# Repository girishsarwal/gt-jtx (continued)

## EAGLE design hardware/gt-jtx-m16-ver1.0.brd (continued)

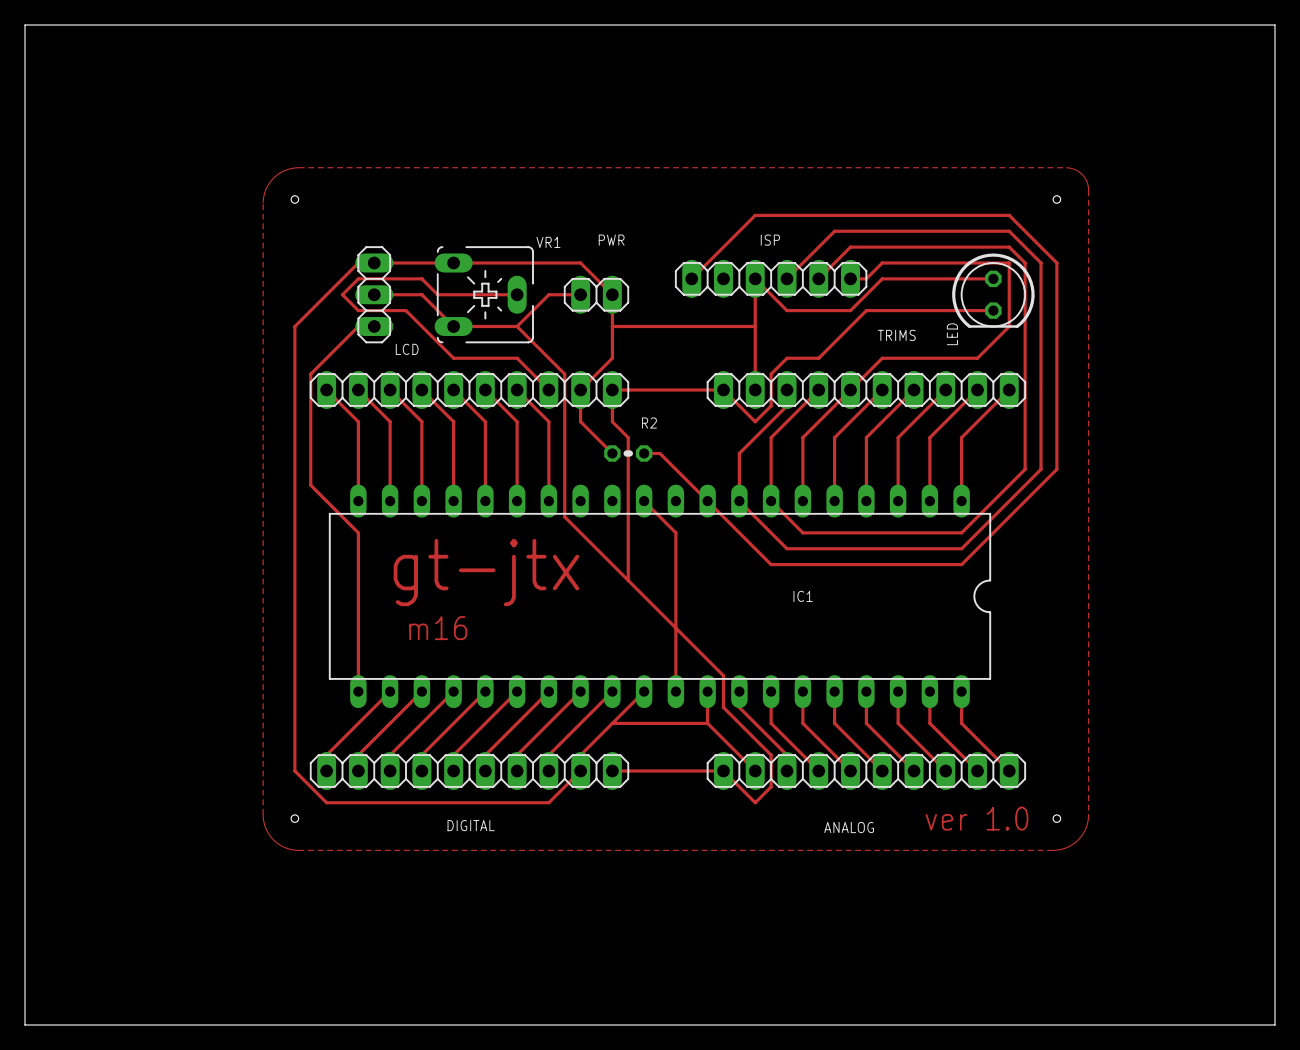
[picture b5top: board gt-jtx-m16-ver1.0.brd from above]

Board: 2 copper layers, 100.0 x 80.0 mm, 11 parts (0 on the bottom side), 36 nets.

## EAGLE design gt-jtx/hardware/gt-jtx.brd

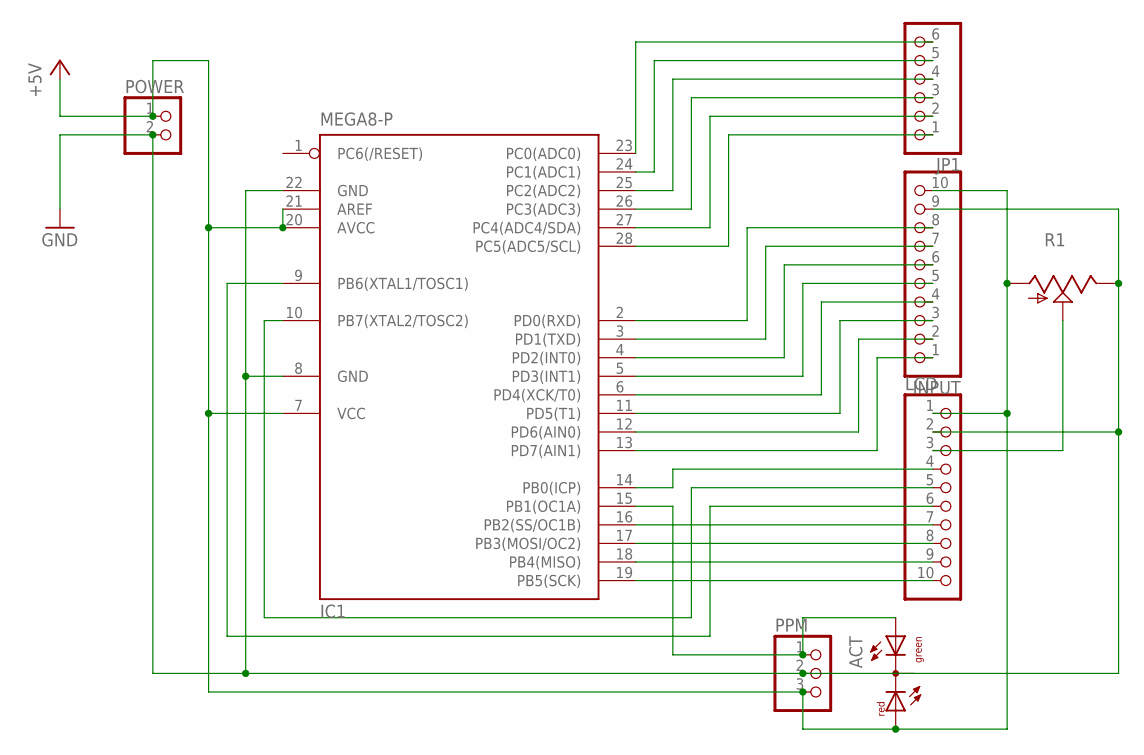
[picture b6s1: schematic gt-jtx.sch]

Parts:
ACT: DUOLED-RG-C; DUOLED-C-5MM
IC1: MEGA8-P; DIL28-3
INPUT: PINHD-1X10; 1X10
JP1: PINHD-1X6; 1X06
LCD: PINHD-1X10; 1X10
POWER: PINHD-1X2; 1X02
PPM: PINHD-1X3; 1X03
R1: TRIM_US-CA6V; CA6V

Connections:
+5V: ACT.AR, IC1.7 (VCC), IC1.20 (AVCC), IC1.21 (AREF), INPUT.10, LCD.1, POWER.1, PPM.3, R1.A; also elsewhere on the board
GND: ACT.C, IC1.8 (GND), IC1.22 (GND), INPUT.9, LCD.2, POWER.2, PPM.2, R1.E
unnamed: IC1.23 (PC0(ADC0)), JP1.6
unnamed: IC1.24 (PC1(ADC1)), JP1.5
unnamed: IC1.25 (PC2(ADC2)), JP1.4
unnamed: IC1.26 (PC3(ADC3)), JP1.3
unnamed: IC1.14 (PB0(ICP)), LCD.4
unnamed: IC1.10 (PB7(XTAL2/TOSC2)), LCD.5
unnamed: IC1.9 (PB6(XTAL1/TOSC1)), LCD.6
unnamed: IC1.2 (PD0(RXD)), INPUT.8
unnamed: LCD.3, R1.S
unnamed: IC1.27 (PC4(ADC4/SDA)), JP1.2
unnamed: IC1.28 (PC5(ADC5/SCL)), JP1.1
unnamed: IC1.19 (PB5(SCK)), LCD.10
unnamed: IC1.18 (PB4(MISO)), LCD.9
unnamed: IC1.17 (PB3(MOSI/OC2)), LCD.8
unnamed: IC1.16 (PB2(SS/OC1B)), LCD.7
unnamed: ACT.AX (AG), IC1.15 (PB1(OC1A)), PPM.1
unnamed: IC1.3 (PD1(TXD)), INPUT.7
unnamed: IC1.4 (PD2(INT0)), INPUT.6
unnamed: IC1.5 (PD3(INT1)), INPUT.5
unnamed: IC1.6 (PD4(XCK/T0)), INPUT.4
unnamed: IC1.11 (PD5(T1)), INPUT.3
unnamed: IC1.13 (PD7(AIN1)), INPUT.1
unnamed: IC1.12 (PD6(AIN0)), INPUT.2
unnamed 26: IC1.1 (PC6(/RESET)); also elsewhere on the board

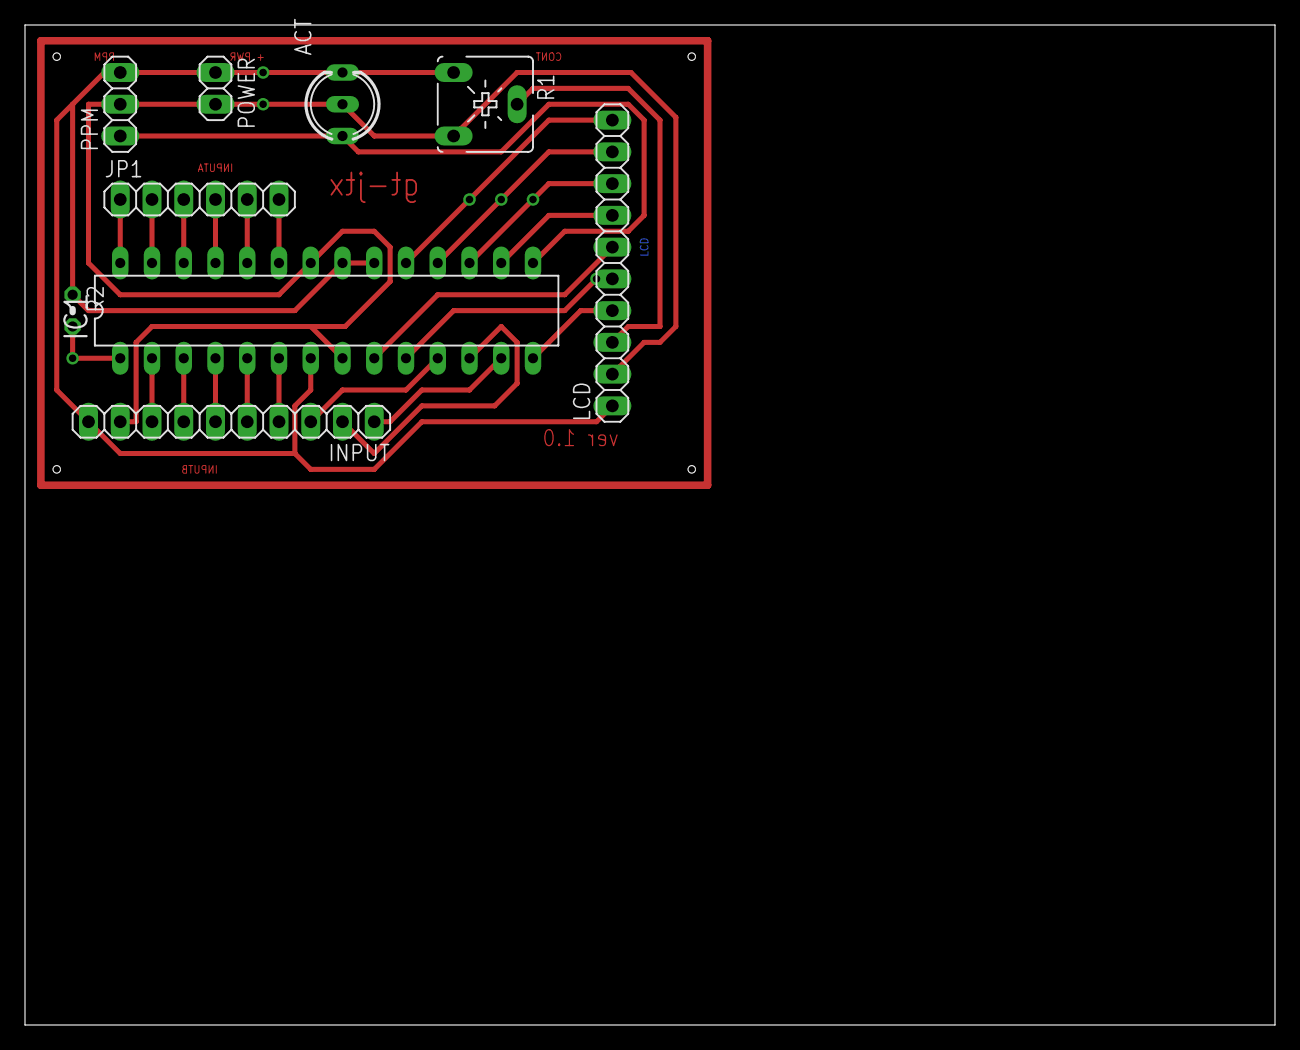
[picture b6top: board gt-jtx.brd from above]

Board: 2 copper layers, 100.0 x 80.0 mm, 9 parts (0 on the bottom side), 26 nets.

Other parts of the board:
R2: 0204V

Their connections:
+5V: R2.1; also elsewhere on the board
unnamed 26: R2.2; also elsewhere on the board

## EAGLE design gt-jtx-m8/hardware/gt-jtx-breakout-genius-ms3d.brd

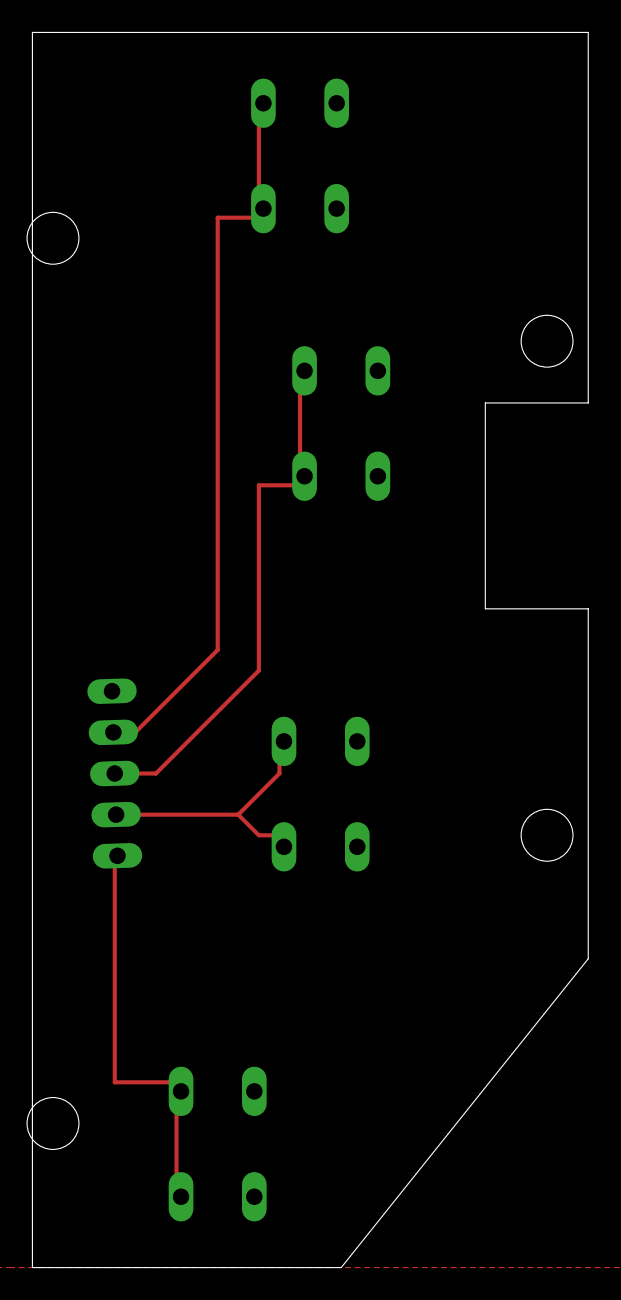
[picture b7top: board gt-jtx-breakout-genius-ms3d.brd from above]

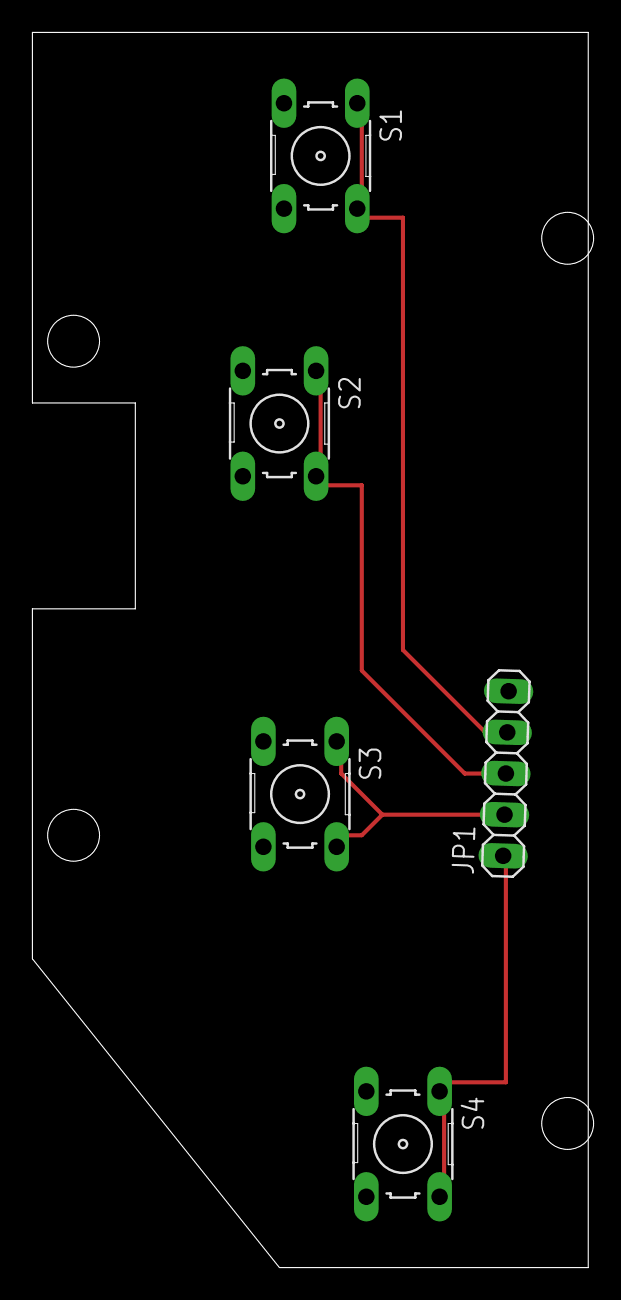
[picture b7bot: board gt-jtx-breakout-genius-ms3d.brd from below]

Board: 2 copper layers, 34.3 x 76.2 mm, 5 parts (5 on the bottom side), 5 nets.

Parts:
JP1: 1X05
S1, S2, S3, S4: B3F-10XX

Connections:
GND: JP1.5, S1.3, S1.4, S2.3, S2.4, S3.3, S3.4, S4.3, S4.4
unnamed: JP1.2, S3.1, S3.2
unnamed: JP1.1, S4.1, S4.2
unnamed: JP1.4, S1.1, S1.2
unnamed: JP1.3, S2.1, S2.2

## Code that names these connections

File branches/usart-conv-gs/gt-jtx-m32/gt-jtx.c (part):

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#define MAGIC_NUMBER 0xA0


#define INP1		0    //Mapped to PA7
#define INP2		1    //Mapped to PA6
#define INP3		2    //Mapped to PA5
#define INP4		3    //Mapped to PA4
#define INP5 		4    //Mapped to PA3
#define INP6		5    //Mapped to PA2
#define INP7		6    //Mapped to PA1
#define INP8		7    //Mapped to PA0

#define MAX_ANALOG_INPUTS 8

#define INP9		8     //Mapped to PD6
#define INP10		9     //Mapped to PD3
#define INP11		10    //Mapped to PD2
#define INP12		11    //Mapped to PB4
#define INP13		12    //Mapped to PB3
#define INP14		13    //Mapped to PB2
#define INP15		14    //Mapped to PB1
#define INP16		15     //Mapped to PB0

#define MAX_DIGITAL_INPUTS 8

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	/** setup the SPI Slave **/
	/** Port B has the MISO/MOSI pins. Setup MOSI as input **/
	transaction.state = WAIT_OPCODE;
	DDRB = (1<<PB6);	/**Setup MISO as output */
	SPCR = (1<<SPE) | (1<<SPIE) | (1<<SPR0) | (1<<SPR1)| (1<<CPOL);	/** enable SPI **/
	SPDR = 0xFF;
	sei();
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	DDR_ANALOG = 0x00;						
	PORT_ANALOG = 0x00;				/**Deactivate any pull ups **/
											/**
											 ** PC0 = AIL Input
											 ** PC1 = ELE Input
											 ** PC2 = THR Input
											 ** PC3 = RUD Input
											 ** PC4 = CH5 Input
											 ** PC5 - CH6 Input
											 ** PC6 - CH7 Input
											 ** PC7 - Ch8 Input
											**/
 	
 	/** Trim switches **/
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
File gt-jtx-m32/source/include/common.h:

/*
 * common.h
 *
 *  Created on: 22-May-2018
 *      Author: Girish Sarwal
 *      Email:  g.sarwal@gmail.com
 *      	 , 	girish.sarwal@gluedtomatoes.com
 */

#ifndef _COMMON_H_
#define _COMMON_H_

#ifndef F_CPU
#define F_CPU 1000000UL
#endif

#define BAUDRATE 19200	/** USART Baudrate **/
#define UBRRVAL ((F_CPU/(BAUDRATE*16UL))-1)

#define DEBUG

#include <avr/io.h>
#include <util/delay.h>
#include <avr/eeprom.h>
#include <avr/interrupt.h>
#include <math.h>

/** Analog inputs are 0-7 on Port A**/
#define PORT_ANALOG	PORTA
#define DDR_ANALOG	DDRA
#define PIN_ANALOG	PINA

#define AI0		0    //Mapped to PA0
#define AI1		1    //Mapped to PA1
#define AI2		2    //Mapped to PA2
#define AI3		3    //Mapped to PA3
#define AI4 	4    //Mapped to PA4
#define AI5		5    //Mapped to PA5
#define AI6		6    //Mapped to PA6
#define AI7		7    //Mapped to PA7


#define NUM_ANALOG_INPUTS 8

#define PORT_DIGITAL	PORTB
#define DDR_DIGITAL		DDRB
#define PIN_DIGITAL		PINB

/** Digital inputs are 0-7 on Port B **/
#define DI0		0    //Mapped to PB0
#define DI1		1    //Mapped to PB1
#define DI2		2    //Mapped to PB2
#define DI3		3    //Mapped to PB3
#define DI4 	4    //Mapped to PB4
#define DI5		5    //Mapped to PB5
#define DI6		6    //Mapped to PB6
#define DI7		7    //Mapped to PB7

#define NUM_DIGITAL_INPUTS 8

#define NUM_PHYSICAL_INPUTS (NUM_ANALOG_INPUTS + NUM_DIGITAL_INPUTS)

#define	INP0 	AI0
#define INP1	AI1
#define INP2	AI2
#define INP3	AI3
#define INP4	AI4
#define INP5	AI5
#define INP6	AI6
#define INP7	AI7

#define INP8	NUM_ANALOG_INPUTS + DI0
#define INP9	NUM_ANALOG_INPUTS + DI1
#define INP10	NUM_ANALOG_INPUTS + DI2
#define INP11	NUM_ANALOG_INPUTS + DI3
#define INP12	NUM_ANALOG_INPUTS + DI4
#define INP13	NUM_ANALOG_INPUTS + DI5
#define INP14	NUM_ANALOG_INPUTS + DI6
#define INP15	NUM_ANALOG_INPUTS + DI7

/** Digital inputs are represented by index following the first 16 inputs**/

#define VINP0		16
#define VINP1		17
#define VINP2		18
#define VINP3		19
#define VINP4		20
#define VINP5		21
#define VINP6		22
#define VINP7		23

#define NUM_VIRTUAL_INPUTS 8

#define CH1		0		//Mapped to A
#define CH2		1		//Mapped to E
#define CH3		2		//Mapped to T
#define CH4		3		//Mapped to R
#define CH5		4		//Mapped to 5
#define CH6		5		//Mapped to 6
#define CH7		6		//Mapped to 7
#define CH8		7		//Mapped to 8

/** total inputs are the sum of all **/
#define NUM_INPUTS (NUM_ANALOG_INPUTS + NUM_DIGITAL_INPUTS + NUM_VIRTUAL_INPUTS)

/** Trim ports **/
#define PORT_TRIM		PORTC
#define DDR_TRIM		DDRC
#define PIN_TRIM		PINC

#define SIG_TRIM_CH1_PLUS 		0
#define SIG_TRIM_CH1_MINUS 		1
#define SIG_TRIM_CH2_PLUS 		2
#define SIG_TRIM_CH2_MINUS 		3
#define SIG_TRIM_CH3_PLUS 		4
#define SIG_TRIM_CH3_MINUS 		5
#define SIG_TRIM_CH4_PLUS 		6
#define SIG_TRIM_CH4_MINUS 		7

#define TRIM_UPPER_END 200
#define TRIM_LOWER_END 0
#define TRIM_CENTER 100

/** Output Port Mappings **/

#define NUM_OUTPUTS	8
#define SYNC NUM_OUTPUTS
#define NUM_OUTPUTS_INCLUDING_SYNC	(NUM_OUTPUTS + 1)

/** PPM is output on Port D **/
#define PORT_PPM		PORTD
#define DDR_PPM		DDRD
#define PIN_PPM		PIND

/** Speaker for voice **/
#define PORT_SPEAK		PORTD
#define DDR_SPEAK		DDRD

#define SIG_PPM		5
#define SIG_SPEAK	4

#define HIBYTE(x) (x >> 8)
#define LOBYTE(x) (x & 0xFF)

#define HIWORD(x) (x >> 4)
#define LOWORD(x) (x & 0xF0)

#define FRAME_START 0x7E
#define FRAME_END 0x7E
#define DLE 0x7D
#define SUBS(x)	x ^ 0x20

#define US_TO_TICKS(x) (x * ((F_CPU/1000)/1000))

void memset16(uint16_t* a, uint16_t value, uint8_t size);

#define MAX_BUFFER_SIZE 128
enum BUFFER_STATUS {
	BUFFER_OK,
	BUFFER_EMPTY,
	BUFFER_FULL,
};


#define DEFAULT_SETUP_STATE	252
#define DEFAULT_MIN_SIGNAL_WIDTH 700
#define DEFAULT_MAX_SIGNAL_WIDTH 1700
#define DEFAULT_INTER_CHANNEL_WIDTH 300
#define DEFAULT_FRAME_WIDTH 22500
#define DEFAULT_UPPER_CALIBRATION 0
#define DEFAULT_LOWER_CALIBRATION 1024




#endif /* INCLUDES_COMMON_H_ */

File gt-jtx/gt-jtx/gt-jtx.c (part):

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#endif	
	/** set inputs **/				
	DDRC = 0x00;						/** PORTC in the input for ADC control on ATmega8**/
											/** PC0 = Menu key
											 ** PC1 = AIL Input
											 ** PC2 = ELE Input
											 ** PC3 = THR Input
											 ** PC4 = RUD Input
											 ** PC5 = FLAP Input **/
 	PORTC = 0x01;           		/** Activate Pull Up resistor on MENU KEY ONLY 0b00000001 **/

	DDRD = 0x00;						/** Port D has the trim switches, make them digital input **/
											/** PD0 = AIL+
											 ** PD1 = AIL-
											 ** PD2 = ELE+
											 ** PD3 = ELE-
											 ** PD4 = THR+
											 ** PD5 = THR-
											 ** PD6 = RUD+
											 ** PD7 = RUD- **/
	PORTD = 0xFF; 						/** Activate all pull up resistors on port D 0b11111111 */

	DDRB = 0xFF;						/** make PB1 as out pin **/
	PORTB = 0x20;						/** make PB1 as low **/
	TCNT1 = 0;
	
	TCCR1B |= (1<<CS10) ;				/** F_CPU - 1Mhz Timebase **/
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
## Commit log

2012-09-17 Initial directory structure.
2012-09-20 SYNC: attempted to add a timer
2012-09-21 updated to generate a 22ms timer for rc frame on a 1mhz clock
2012-09-24 successfully getting a configurable timed pulse for rc frame. This needs to be moved onto the hardware pin now
2012-09-24 - fixed array to hold only channels - fixed for 8 channels
2012-09-26 - updated to use hardware output - updated to use PB1 instead of PB2 for output
2012-09-27 Added .prj file for VMLAB
2012-10-03 added input from ADC pins (port A) on atmega 8
2012-10-03 moved to some constants instead of hardcoded values
2012-10-30 added lcd support for 16x2 lcd files added lcd.c, lcd.h channel values for AIL, ELE, THR and RUD shown on display now..values will range between 500 ms and 1500 ms (signal time for the servos)
2012-10-31 updated to output correct RC frame, needs to be verified against a suitable hardware LCD display updated to show percent movements on sticks (between -100 and 100) updated to run on 16 MHz timebase u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
2012-11-16 added USE_LCD_DISPLAY flag to conditional compile for devices without LCD
2012-12-11 added eagle schematic for main board. This is still not complete. Please consider future versions.
2012-12-13 gt-jtx now has a board layout and a schematic.
2012-12-17 added makefile
2012-12-23 Added ISCP pads on board for ATmega8 programming. Increased Route width for better transfer of toner to PCB. Routes are now on bottom layer so no need to mirror image for printing
2012-12-24 changed layer to use top layer.
2012-12-27 added guild photos
2012-12-28 Added Trim inputs to the controls Added Menu and settings to gt-jtx. Not the best but all works
2013-01-05 increased track width wherever possible to reduces chance of undercutting while etching. added necking in some areas of pcb
2013-01-23 added functionality to read from eeprom added calibaration and setting screen (both non working) changed navigation to use menu button
2013-01-25 PARTIAL CHECKIN **CONSIDER FUTURE CHECKINS *** added calibration code added eeprom write for calibration removed a couple of useless function optimized
2013-01-25 copied makefile from VMLAB for building
2013-01-26 Added scripts for erasing chip, flashing chip and flashing eeprom fixed percentage calculation problem
2013-01-28 removed useless pro file from hardware/gt-jtx-breakout.pro added sch and brd files for breakout board
2013-02-11 Added Build Photos Added Format changes to code Fixed display issues Added trim control setting via navigation buttons
2013-02-11 added built photos
2013-02-11 Renaming to m8 to mark as m8 variant
2013-02-11 Project Reorganization
2013-02-14 fixed makefile added code to reverse channels added flaps button to vmlab project file
2013-02-14 Added m32 code branch for development on AVR 32. This is a copy of the ATmega8 branch. Changes due.
2013-02-14 changd makefile format back to sh
2013-02-16 updated makefile to support windows and linux enviroments type make windows to make for windows type make linux to make for linux
2013-02-20 added glcd - working code
2013-02-21 PARTIAL CHECKIN: updted m32 version - not stable - consider future releases
2013-02-21 PARTIAL CHECKIN
2013-02-21 fixe ppm stream for 8 channels
2013-02-22 added basic ui
2013-02-27 added speaker and switch ports changed ppm pin to PD5
2013-02-27 fixed some of the hardware design
2013-02-27 added new font
2013-03-02 added font. stuff updated
2013-03-30 added serial protocol to hardware spec
2014-11-22 Added Atmel studio project Added parenthesis to remove warning
2015-02-26 added model and tx
2015-02-26 PATRTIAL CHECKIN: code comopiles but not tested or debugged
2015-03-02 PARTIAL CHECKIN: fixed problems in m32 version
2015-03-05 added lcd code
2015-03-09 added branches which were not moved during git conversion
2015-03-11 updated serial protocol for comms
2015-04-08 Migrating wiki contents from Google Code
2015-05-08 Added code for Artrix
2015-05-18 - Added render queue support - removed ArtrixRenderer and implemented it in ArtrixView - Added new State SplashState
2015-05-19 Introdcued renderqueue for rendering added DrawableEntity Class Moved inhgeritance of sprite from drawable entity
2015-06-16 added serial interfacing for android
2015-07-24 Added skeleton for setting uniforms in ShaderManager
2015-08-18 Added VertexDescriptor and modded other classes for support
2015-08-18 removed subprject added by mistake
2015-09-10 changed implementation of shader manager.
2015-09-14 fixed code so shaders are loaded correctly and shader attributes can be read correctly
2015-09-15 added code to dynamically identify and add vertexattributes from shader
2015-09-16 attempt to add drawing triangle. the triangle did not come up as expected
2015-10-26 phew! the first rectangle is visible
2015-10-27 - Added setEGLConfigChooser for Compatibility - Fixed Shaders
2015-10-30 Added PredefinedVertexDescriptors.java, Matrix4x4.java, made changes to the way shaders bind to the vertex format
2015-10-30 PARTIAL COMMIT: made changes to load up a sprite, next is loading the textures to check
2015-12-08 added code to run on boot
2015-12-26 changed pin header to 3x2 instead of 1x6 for accomodating a 6 pin isp. correctec pin configurations
2015-12-26 cleaned up directory structure
2015-12-26 renamed directory
2016-06-22 updated gitignore
2016-06-22 added model, model is the single entity that holds the model information
2016-06-23 removed unnecessary lcd files and added eclipse project
2016-06-23 removed a few warnings
2016-07-21 moved helper tools to the correct folder
2016-07-21 removed unnecessary files and changed project structure
2016-07-22 pin numbers are now added as defines
2016-07-22 changed opcodes, and removed unnecessary functions
2016-07-22 fixed constant name change for successful build
2016-07-22 added g_error code
2016-07-22 removed unnecessary space at EOF
2016-10-21 removed isnt a function decl warning
2016-10-21 removed useles warnings during compilation
2016-10-21 changed program data structures
2016-10-21 fixed ppm signal as per new code
2016-10-21 fixed bug with input no mapping to output correctly
2016-10-24 readingsettings from eeprom
2016-10-25 removed uuid, we dont need it
2016-10-26 added hardware schematic png
2016-10-26 skeleton for starting up usart
2016-10-27 PARTIAL: spi comms updated for frames
2016-11-03 updaed opcode
2016-11-03 removed spi stuff, ready to add usart stuff
2016-11-07 added skeleton for serial comm
2016-11-07 added code for setting packet length etc
2017-05-04 added designs for quick build 2560 opentx
2017-05-04 updated code
2017-05-04 added required eagle libraries
2017-05-25 added new files
2017-09-07 added case design, changed the schematic for lcd
2018-05-09 fixed LCD connections and added connector for contrast adjustment
2018-05-14 added sim connector
2018-05-18 updated board design for new firmware mechanics with oled
2018-05-21 added new project and updated mappings
2018-05-21 updated board with led and isp header updated code with newer structure of using rx/tx
2018-05-22 updated structure
2020-01-07 updated to cpp
